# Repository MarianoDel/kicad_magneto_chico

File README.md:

# Placa para el magneto chico hecha en KiCad

Placa para el magneto chico

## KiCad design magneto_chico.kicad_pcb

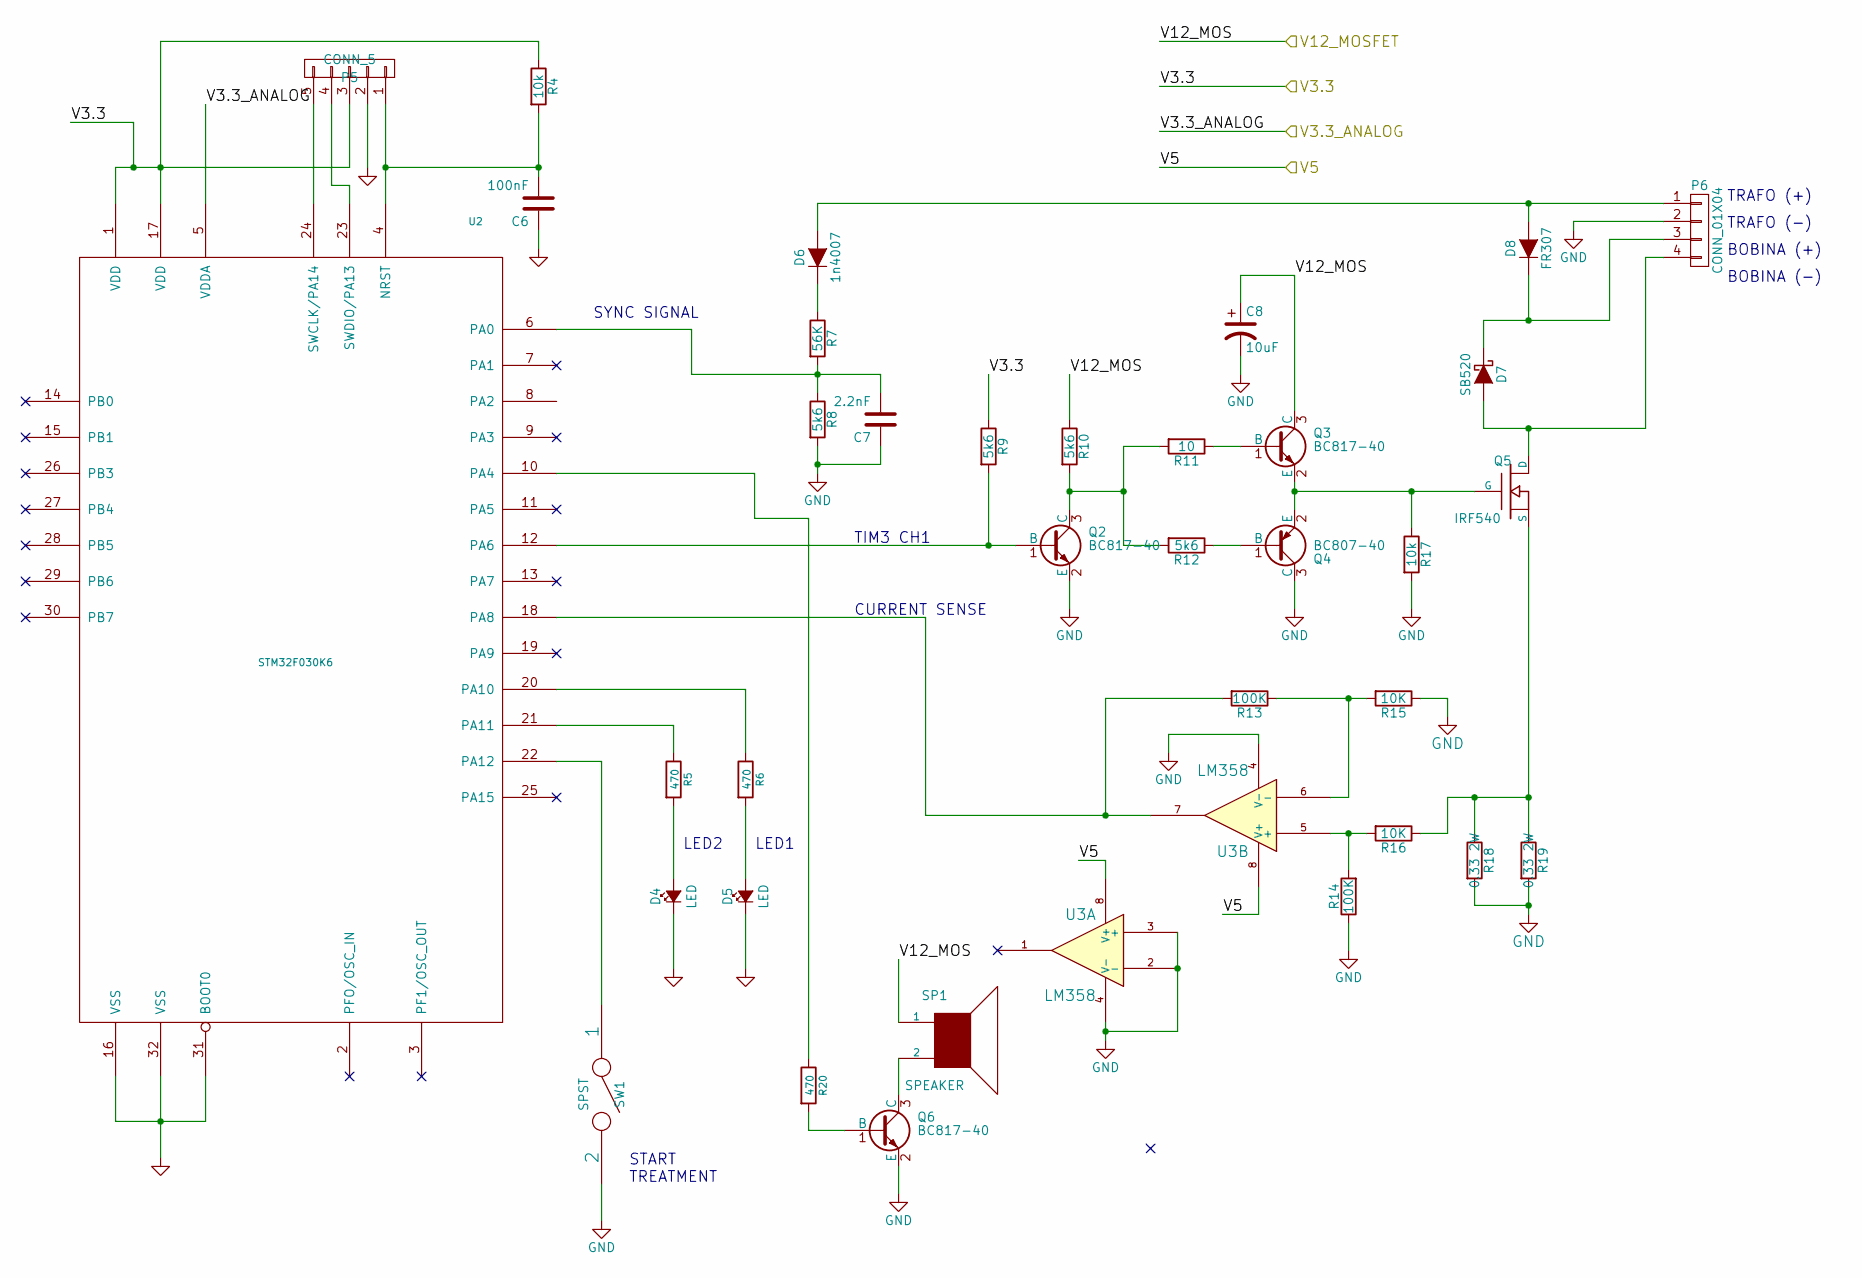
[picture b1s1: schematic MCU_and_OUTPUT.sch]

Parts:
C6: 100nF; C_0805_HandSoldering
C7: 2.2nF; C_0805_HandSoldering
C8: 10uF; C_Radial_D5_L11_P2.5
D4, D5: LED; LED-3MM
D6: 1n4007; DO-214AB_Handsoldering
D7: SB520; Diode_DO-201AD_Horizontal_RM15
D8: FR307; Diode_DO-201AD_Horizontal_RM15
P5: CONN_5; Pin_Header_Straight_1x05
P6: CONN_01X04; bornier4
Q2, Q3, Q6: BC817-40; BC817_SOT-23
Q4: BC807-40; BC857_SOT-23
Q5: IRF540; IRF540N_Vertical
R4: 10k; R_0805_HandSoldering
R5, R6, R20: 470; R_0805_HandSoldering
R7: 56K; R_0805_HandSoldering
R8, R9, R10, R12: 5k6; R_0805_HandSoldering
R11: 10; R_0805_HandSoldering
R13, R14: 100K; R_0805_HandSoldering
R15, R16: 10K; R_0805_HandSoldering
R17: 10k; Resistor_Horizontal_RM7mm
R18, R19: 0.33 2W; Resistor_Horizontal_RM20mm
SP1: SPEAKER; C_Radial_D10_L20_P5
SW1: SPST; Pin_Header_Straight_1x02
U2: STM32F030K6; TQFP-32_7x7mm_Pitch0.8mm
U3: LM358; SO-8

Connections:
/Sheet56FC57FC/V3.3: P5.3, R4.1, R9.1, U2.1 (VDD), U2.17 (VDD); also elsewhere on the board
/Sheet56FC57FC/V3.3_ANALOG: U2.5 (VDDA); also elsewhere on the board
/Sheet56FC57FC/V5: U3.8 (V+); also elsewhere on the board
/Sheet56FC57FC/V12_MOSFET: C8.1, Q3.3 (C), R10.1, SP1.1; also elsewhere on the board
GND: C6.1, C7.1, C8.2, D4.1 (K), D5.1 (K), P5.2, P6.2, Q2.2 (E), Q4.3 (C), Q6.2 (E), R8.2, R14.1, R15.1, R17.2, R18.2, R19.2, SW1.2, U2.16 (VSS), U2.31 (BOOT0), U2.32 (VSS), U3.2 (-), U3.3 (+), U3.4 (V-); also elsewhere on the board
unnamed: C6.2, P5.1, R4.2, U2.4 (NRST)
unnamed: C7.2, R7.2, R8.1, U2.6 (PA0)
unnamed: D4.2 (A), R5.2
unnamed: D5.2 (A), R6.2
unnamed: D6.1 (K), R7.1
unnamed: D6.2 (A), D8.2 (A), P6.1
unnamed: D7.1 (K), D8.1 (K), P6.3
unnamed: D7.2 (A), P6.4, Q5.D
unnamed: P5.4, U2.23 (SWDIO/PA13)
unnamed: P5.5, U2.24 (SWCLK/PA14)
unnamed: Q2.1 (B), R9.2, U2.12 (PA6)
unnamed: Q2.3 (C), R10.2, R11.2, R12.2
unnamed: Q3.1 (B), R11.1
unnamed: Q3.2 (E), Q4.2 (E), Q5.G, R17.1
unnamed: Q4.1 (B), R12.1
unnamed: Q5.S, R16.1, R18.1, R19.1
unnamed: Q6.1 (B), R20.2
unnamed: Q6.3 (C), SP1.2
unnamed: R5.1, U2.21 (PA11)
unnamed: R6.1, U2.20 (PA10)
unnamed: R13.1, R15.2, U3.6 (-)
unnamed: R13.2, U2.18 (PA8), U3.7
unnamed: R14.2, R16.2, U3.5 (+)
unnamed: R20.1, U2.10 (PA4)
unnamed: SW1.1, U2.22 (PA12)

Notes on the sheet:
TIM3 CH1
LED1
LED2
TRAFO (-)
TRAFO (+)
BOBINA (-)
BOBINA (+)
SYNC SIGNAL
CURRENT SENSE
START TREATMENT

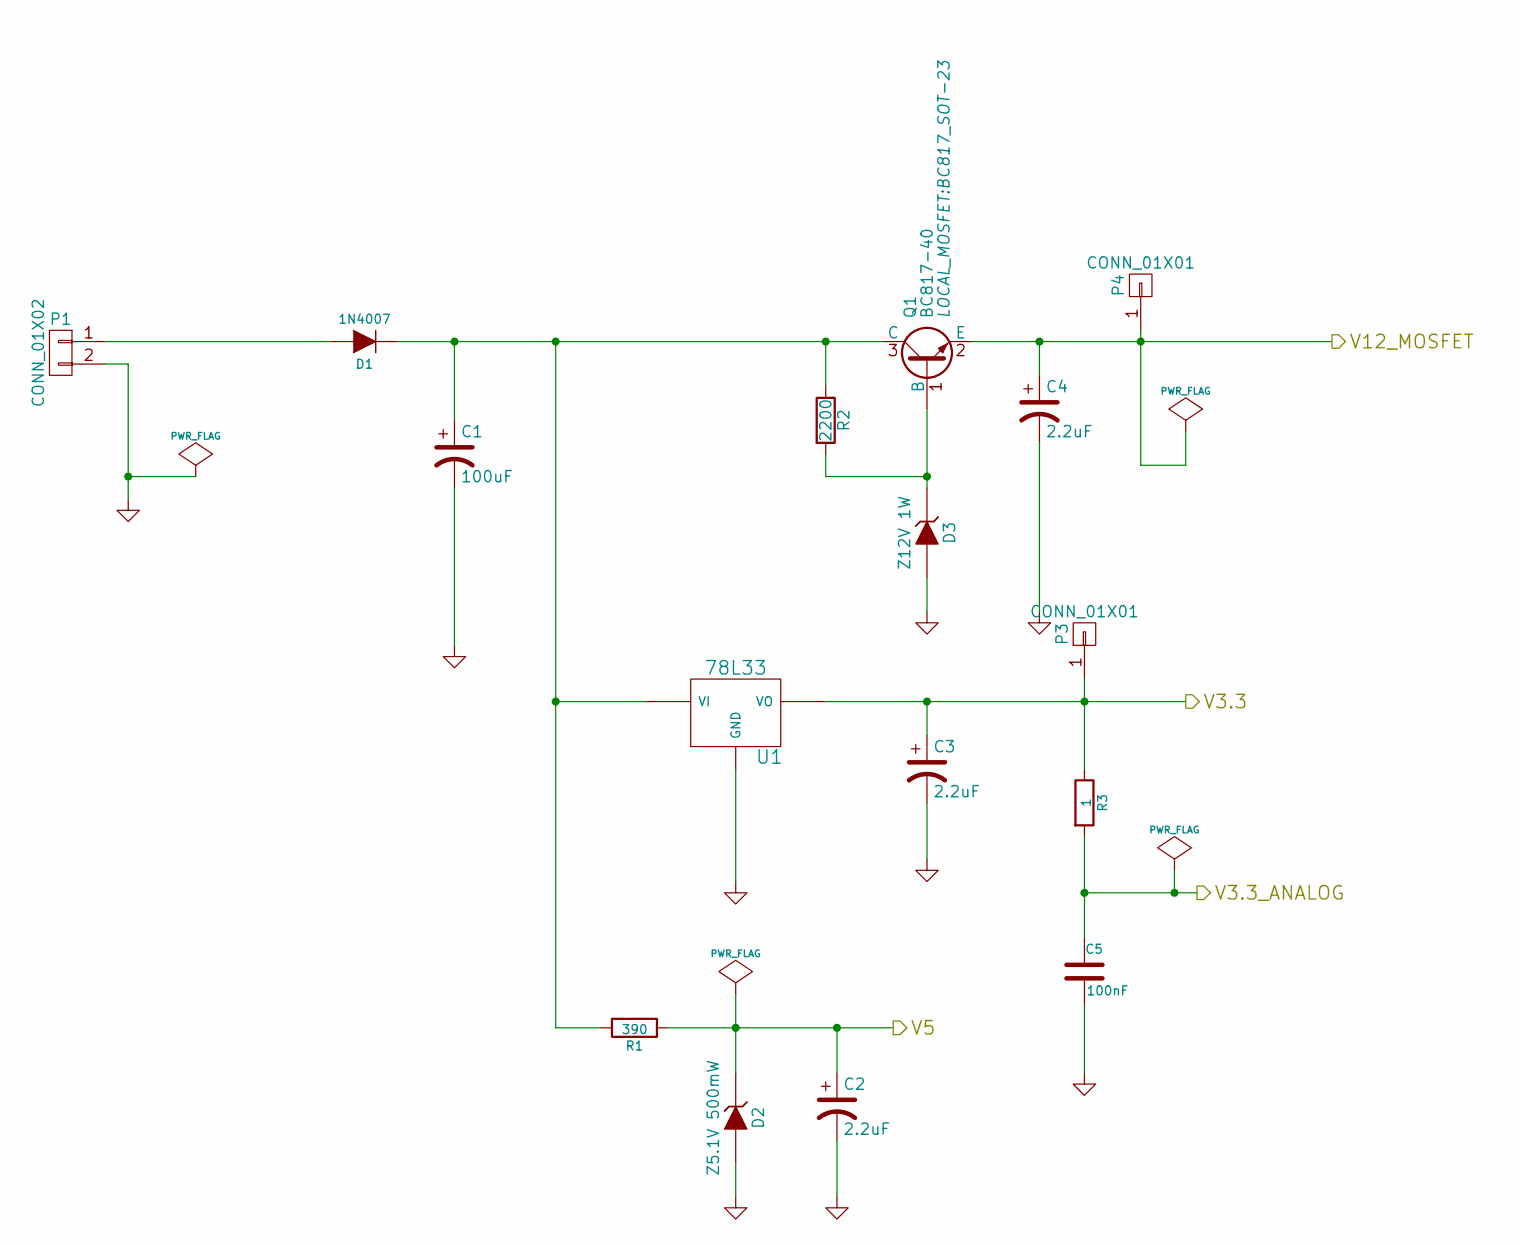
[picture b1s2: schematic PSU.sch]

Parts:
C1: 100uF; C_Radial_D10_L20_P5
C2, C3, C4: 2.2uF; C_Radial_D5_L11_P2.5
C5: 100nF; C_0805_HandSoldering
D1: 1N4007; Diode_DO-41_SOD81_Horizontal_RM10
D2: Z5.1V 500mW; Diode_DO-41_SOD81_Horizontal_RM10
D3: Z12V 1W; MELF_Handsoldering
P1: CONN_01X02; Socket_MOLEX-KK-RM2-54mm_Lock_2pin_straight
P3, P4: CONN_01X01; Pin_Header_Straight_1x01
Q1: BC817-40; BC817_SOT-23
R1: 390; Resistor_Horizontal_RM7mm
R2: 2200; R_0805_HandSoldering
R3: 1; R_0805_HandSoldering
U1: 78L33; TO-92_Inline_Wide

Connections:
/Sheet56FC57FC/V3.3: C3.1, P3.1, R3.1, U1.1 (VO); also elsewhere on the board
/Sheet56FC57FC/V3.3_ANALOG: C5.1, R3.2; also elsewhere on the board
/Sheet56FC57FC/V5: C2.1, D2.1 (K), R1.1; also elsewhere on the board
/Sheet56FC57FC/V12_MOSFET: C4.1, P4.1, Q1.2 (E); also elsewhere on the board
GND: C1.2, C2.2, C3.2, C4.2, C5.2, D2.2 (A), D3.2 (A), P1.2, U1.2 (GND); also elsewhere on the board
unnamed: C1.1, D1.1 (K), Q1.3 (C), R1.2, R2.1, U1.3 (VI)
unnamed: D1.2 (A), P1.1
unnamed: D3.1 (K), Q1.1 (B), R2.2

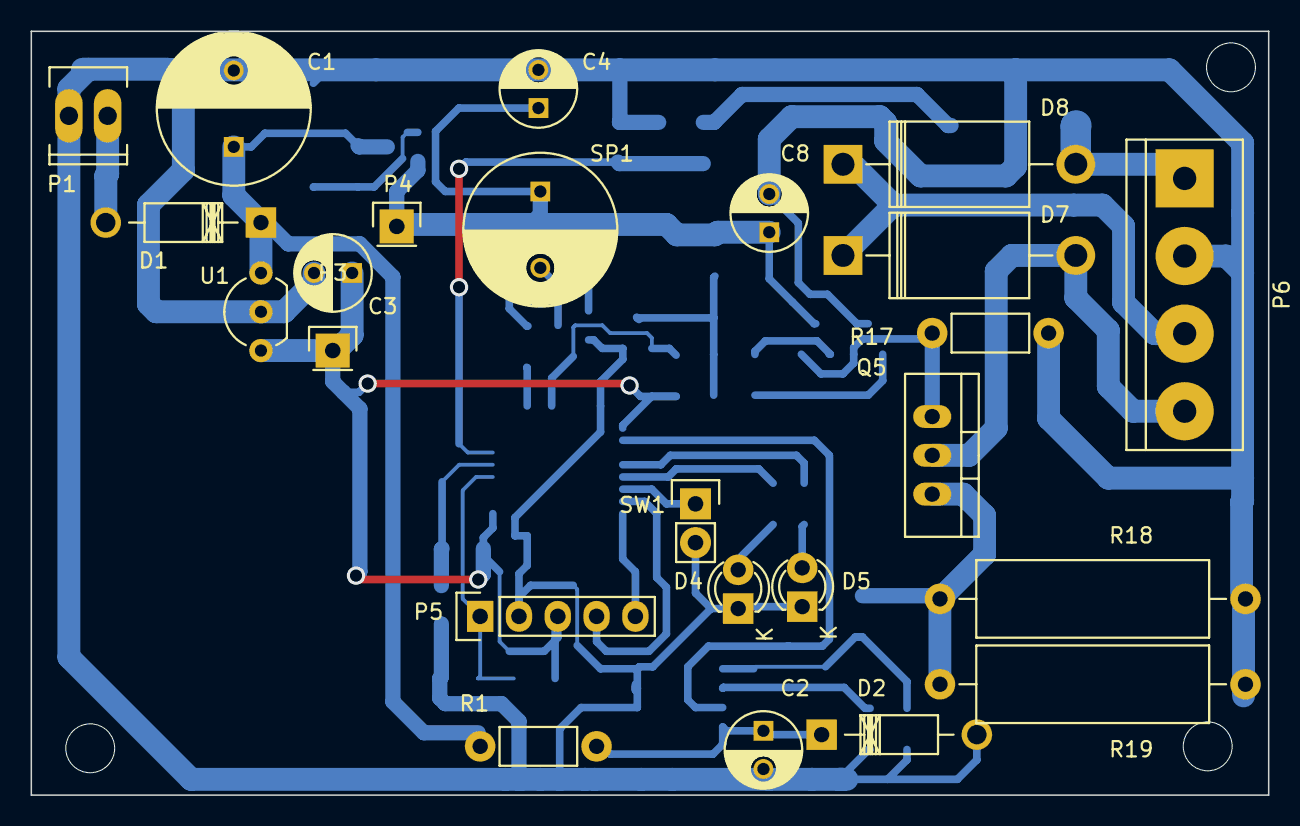
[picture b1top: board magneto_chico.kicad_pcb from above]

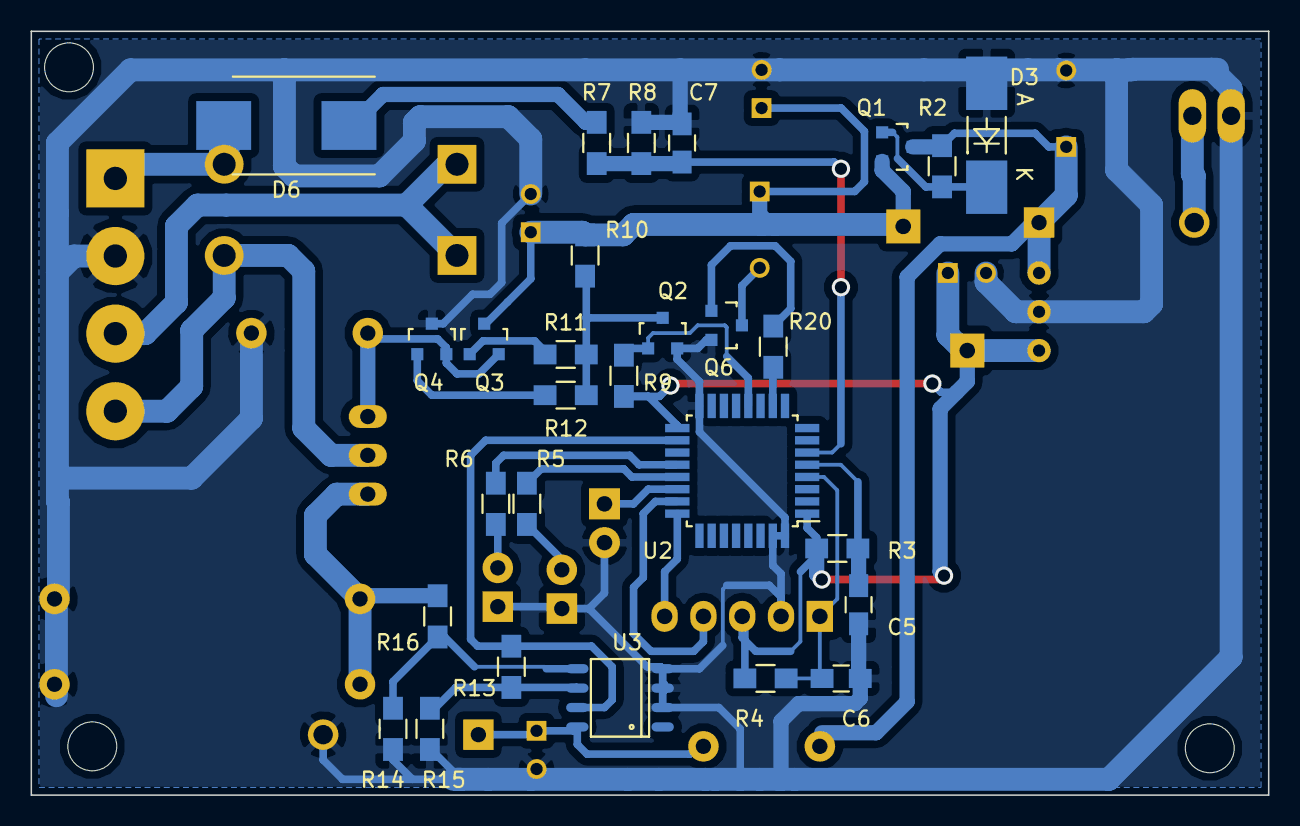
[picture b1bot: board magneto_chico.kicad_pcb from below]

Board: 2 copper layers, 81.0 x 50.0 mm, 52 parts (28 on the bottom side), 33 nets.

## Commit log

2016-03-31 agrego .gitignore
2016-03-31 borro los .bak
2016-04-02 agregue pulsador de arranque y buzzer
2016-04-03 agrego librerias de footprint y paso todo al PCB
2016-04-03 ahora si, todos los footp al PCB
2016-04-03 empiezo a rutear
2016-04-03 mas pistas pero sin micro
2016-04-09 mas routeado casi terminado
2016-04-09 mejor ruteo, faltan 3 pistas
2016-04-10 todo ruteado y pasa DRC
2016-04-30 todo termiando con plano de masa y pines .2
